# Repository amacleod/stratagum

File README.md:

Strata-Gum Tactical Keypad
==========================

Small mechanical keypad for arrow keys, such as for entering stratagems in Helldivers II.

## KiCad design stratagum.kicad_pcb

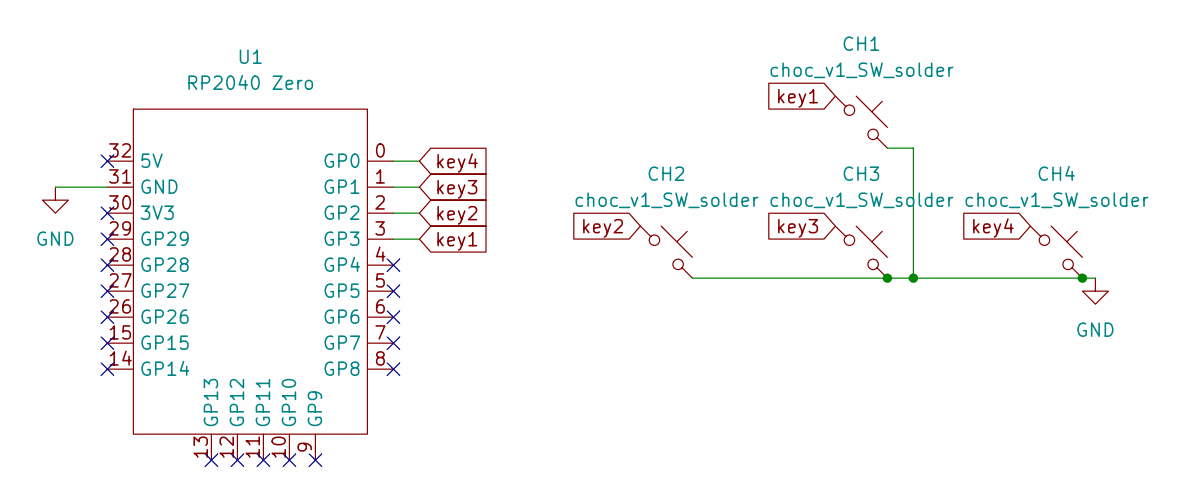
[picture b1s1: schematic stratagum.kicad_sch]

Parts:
CH1, CH2, CH3, CH4: choc_v1_SW_solder; SW_choc_v2_1u
U1: RP2040 Zero; RP2040 Zero (Through Hole)

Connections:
GND: CH1.2, CH2.2, CH3.2, CH4.2, U1.31 (GND)
key1: CH1.1, U1.3 (GP3)
key2: CH2.1, U1.2 (GP2)
key3: CH3.1, U1.1 (GP1)
key4: CH4.1, U1.0 (GP0)

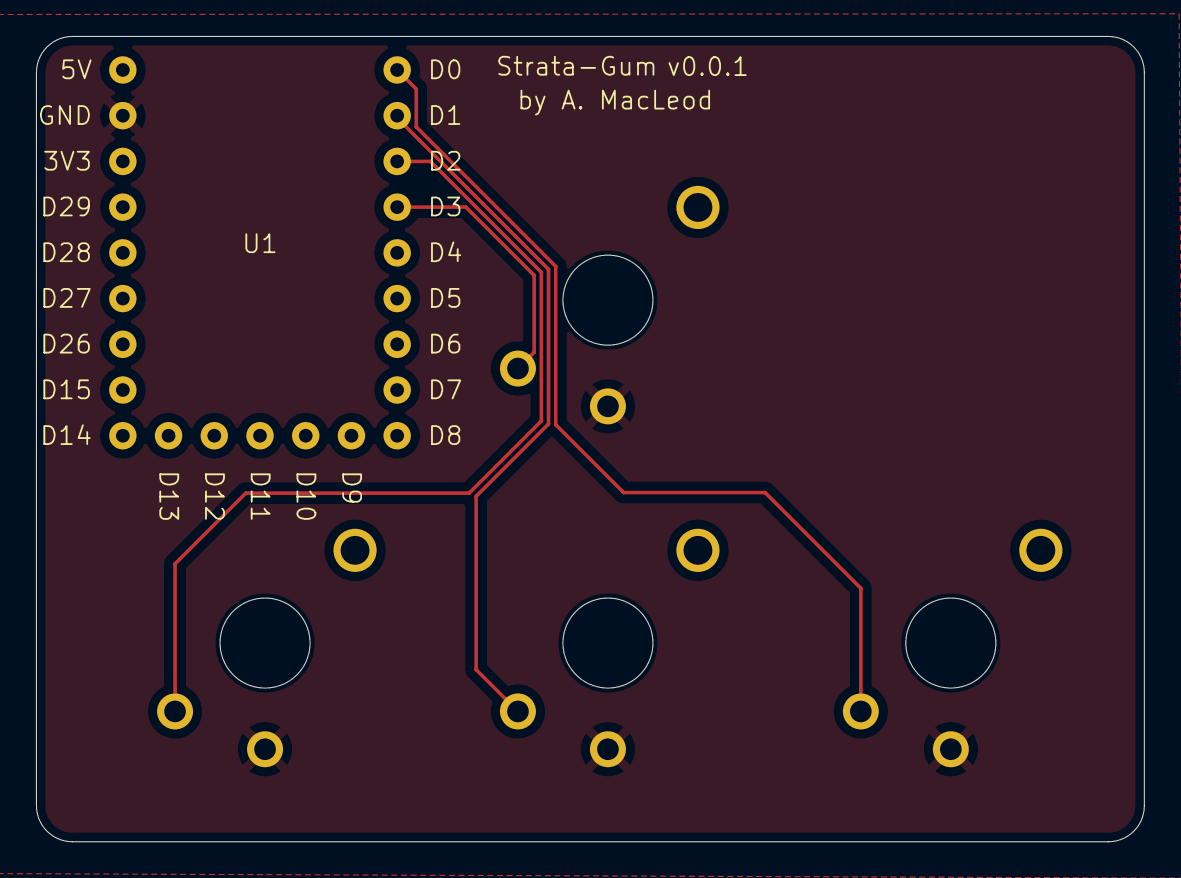
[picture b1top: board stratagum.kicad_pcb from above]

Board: 2 copper layers, 61.5 x 44.7 mm, 5 parts (0 on the bottom side), 5 nets.

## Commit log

2025-06-10 Blank KiCad project for Stratagum.
2025-06-10 Placing symbols for 4-key pad.
2025-06-10 Footprints placed for controller and key switches.
2025-06-10 Gerber ZIP for Strata-Gum v0.0.1
2025-06-10 Adding PCB render to README.
2025-06-10 Ignore lock files from KiCad.
